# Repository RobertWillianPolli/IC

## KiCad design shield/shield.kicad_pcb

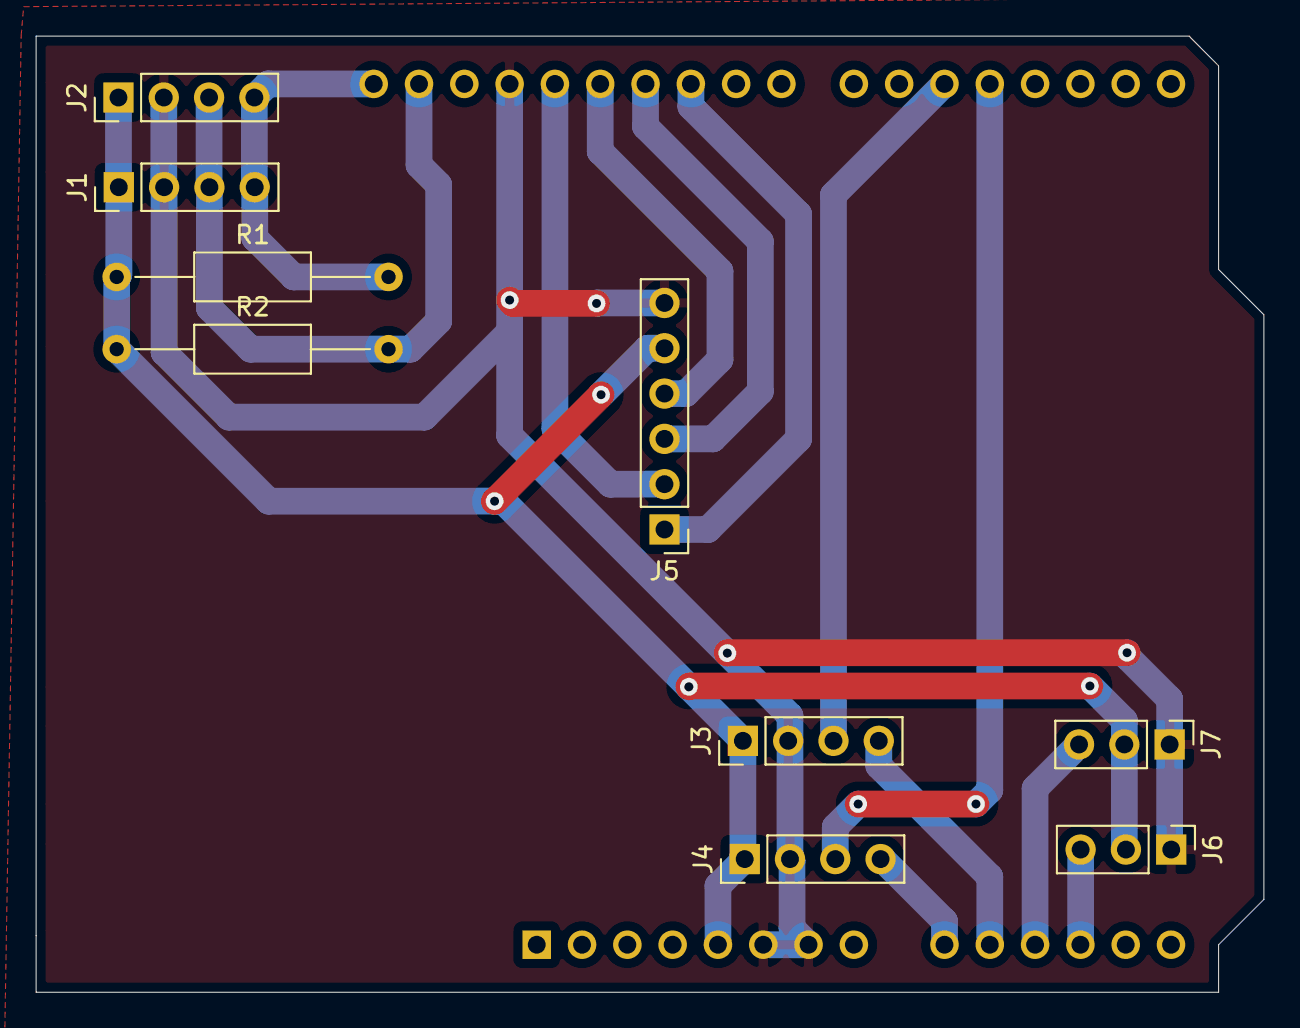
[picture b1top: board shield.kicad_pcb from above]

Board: 2 copper layers, 68.8 x 53.6 mm, 10 parts (1 on the bottom side), 14 nets.

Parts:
A1: Arduino_Leonardo; Arduino_UNO_R3
J1, J2: Screw_Terminal_01x04; PinHeader_1x04_P2.54mm_Vertical
J3, J4: Conn_01x04_Male; PinHeader_1x04_P2.54mm_Vertical
J5: SD_Card; PinHeader_1x06_P2.54mm_Vertical
J6, J7: Conn_01x03_Male; PinHeader_1x03_P2.54mm_Vertical
R1, R2: 4k7; R_Axial_DIN0207_L6.3mm_D2.5mm_P15.24mm_Horizontal

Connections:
/A0: A1.9, J4.4
/A1: A1.10, J3.4
/A2: A1.11, J7.3
/A3: A1.12, J6.3
/CLK: A1.28, J5.2
/CS: A1.25, J5.1
/D0: A1.19, J4.3
/D1: A1.20, J3.3
/MISO: A1.27, J5.4
/MOSI: A1.26, J5.3
/SCL: A1.32, J1.4, J2.4, R1.2
/SDA: A1.31, J1.3, J2.3, R2.2
GND: A1.6, A1.7, A1.29, J1.2, J2.2, J3.2, J4.2, J5.6, J6.1, J7.1
VCC: A1.5, J1.1, J2.1, J3.1, J4.1, J5.5, J6.2, J7.2, R1.1, R2.1

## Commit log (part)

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2026-06-25 Alterado scri´ts para funções
2026-06-26 Testes iniciais
